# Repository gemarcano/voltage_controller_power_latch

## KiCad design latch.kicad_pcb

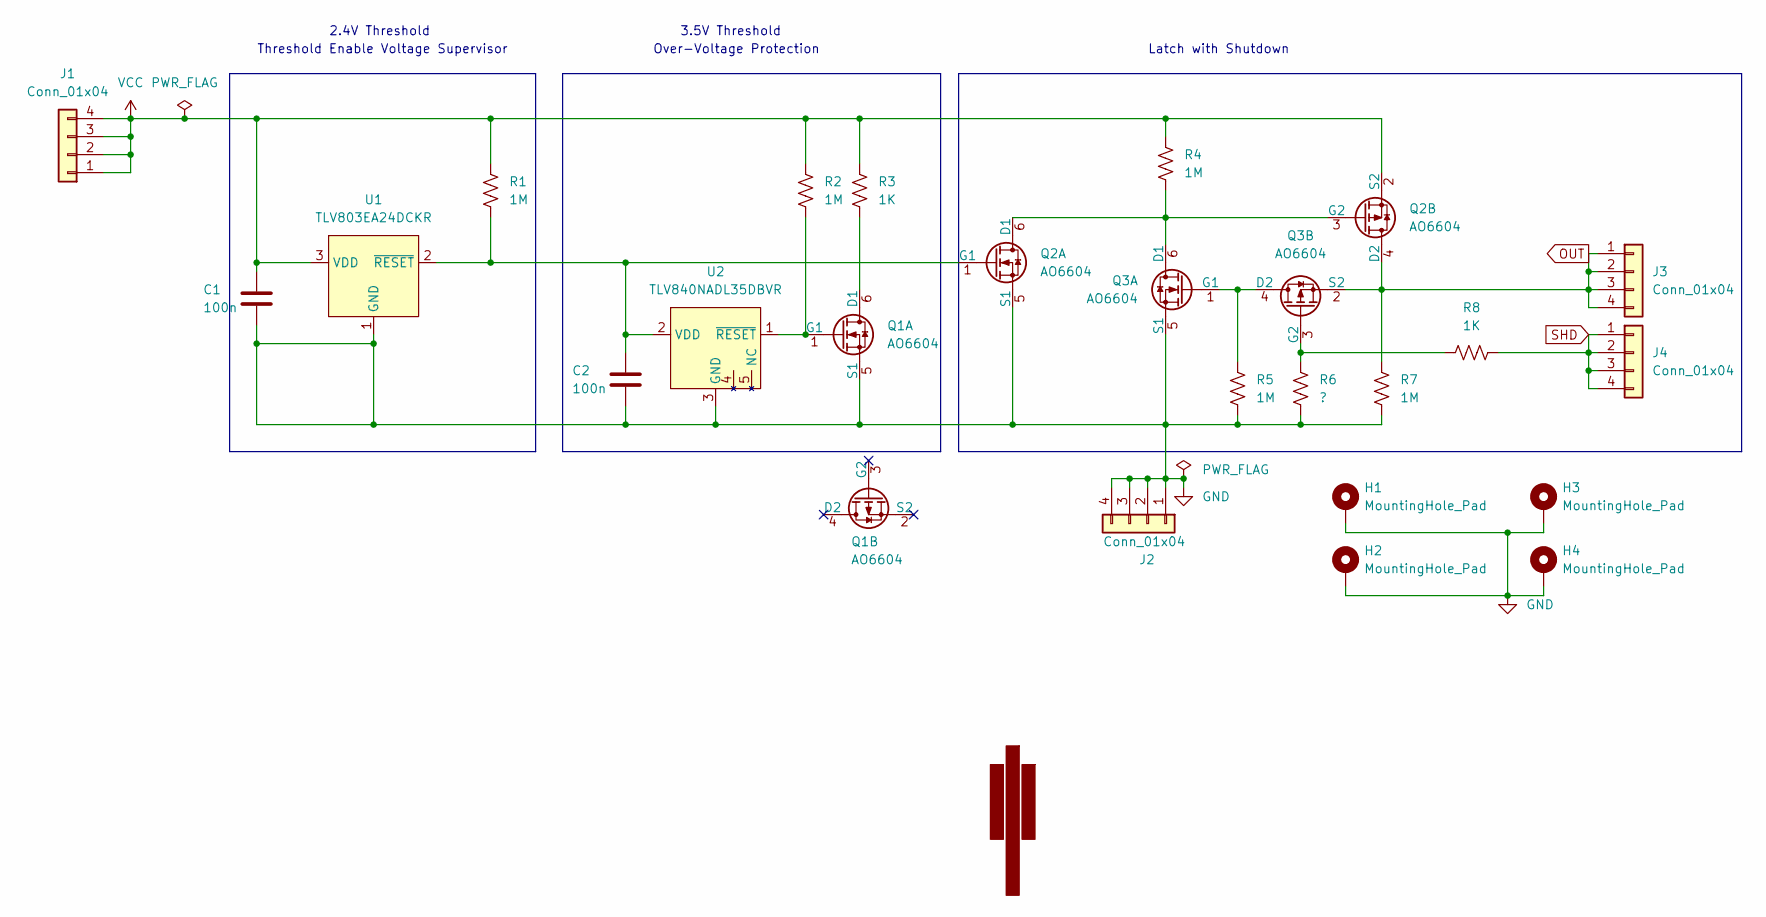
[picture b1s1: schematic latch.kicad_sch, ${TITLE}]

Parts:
C1, C2: 100n; C_0603_1608Metric_Pad1.08x0.95mm_HandSolder
G1: LOGO; smaller_logo
H1, H2, H3, H4: MountingHole_Pad; MountingHole_3.2mm_M3_Pad_Via
J1, J2, J3, J4: Conn_01x04; PinHeader_1x04_P2.54mm_Vertical
Q1, Q2, Q3: AO6604; SOT-457_Handsolder
R1, R2, R4, R5, R7: 1M; R_0603_1608Metric_Pad0.98x0.95mm_HandSolder
R3, R8: 1K; R_0603_1608Metric_Pad0.98x0.95mm_HandSolder
R6: ?; R_0603_1608Metric_Pad0.98x0.95mm_HandSolder
U1: TLV803EA24DCKR; SOT-323_SC-70_Handsoldering
U2: TLV840NADL35DBVR; SOT-23-5_HandSoldering

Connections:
GND: C1.2, C2.2, H1.1, H2.1, H3.1, H4.1, J2.1, J2.2, J2.3, J2.4, Q1.5 (S1), Q2.5 (S1), Q3.5 (S1), R5.2, R6.2, R7.2, U1.1 (GND), U2.3 (GND)
unnamed: C2.1, Q2.1 (G1), R1.1, U1.2 (~RESET), U2.2 (VDD)
unnamed: Q1.1 (G1), R2.2, U2.1 (~RESET)
unnamed: Q1.6 (D1), R3.2
unnamed: Q2.3 (G2), Q2.6 (D1), Q3.6 (D1), R4.2
unnamed: Q3.1 (G1), Q3.4 (D2), R5.1
unnamed: Q3.3 (G2), R6.1, R8.1
OUT: J3.1, J3.2, J3.3, J3.4, Q2.4 (D2), Q3.2 (S2), R7.1
SHD: J4.1, J4.2, J4.3, J4.4, R8.2
VCC: C1.1, J1.1, J1.2, J1.3, J1.4, Q2.2 (S2), R1.2, R2.1, R3.1, R4.1, U1.3 (VDD)

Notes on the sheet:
Threshold Enable Voltage Supervisor
Over-Voltage Protection
3.5V Threshold
Latch with Shutdown
2.4V Threshold

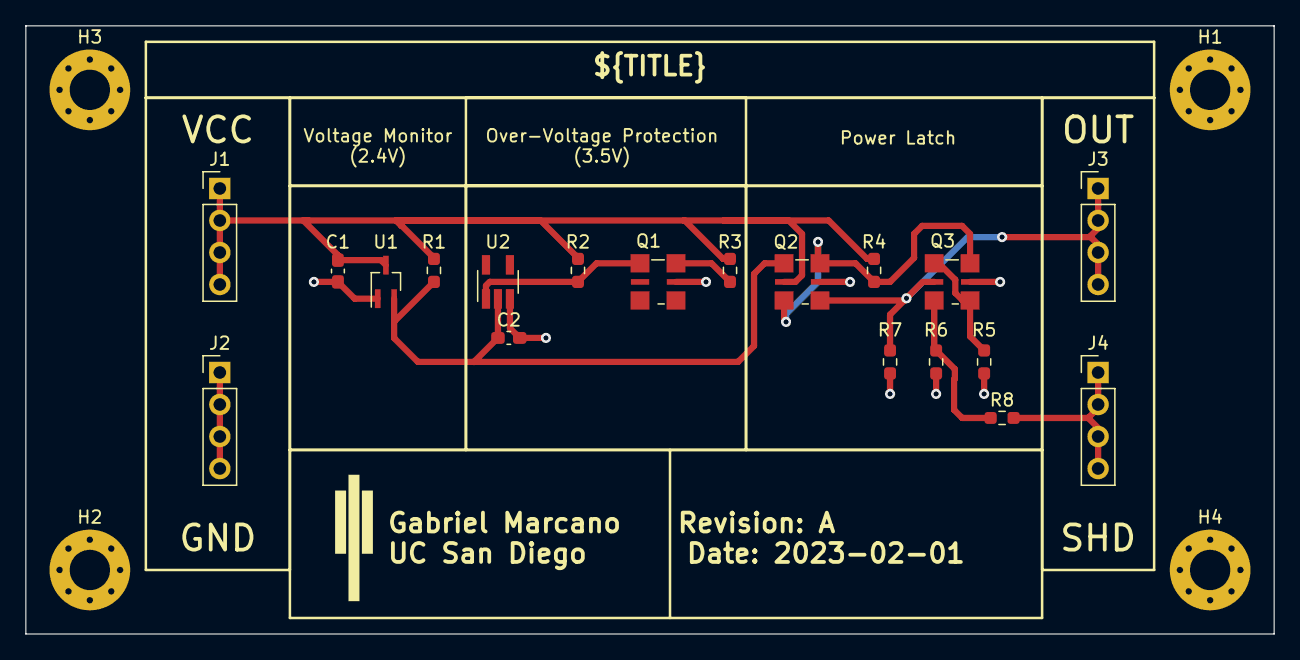
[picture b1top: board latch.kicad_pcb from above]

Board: 2 copper layers, 99.1 x 48.3 mm, 24 parts (0 on the bottom side), 10 nets.

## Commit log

2023-02-02 Add PCB drawing
